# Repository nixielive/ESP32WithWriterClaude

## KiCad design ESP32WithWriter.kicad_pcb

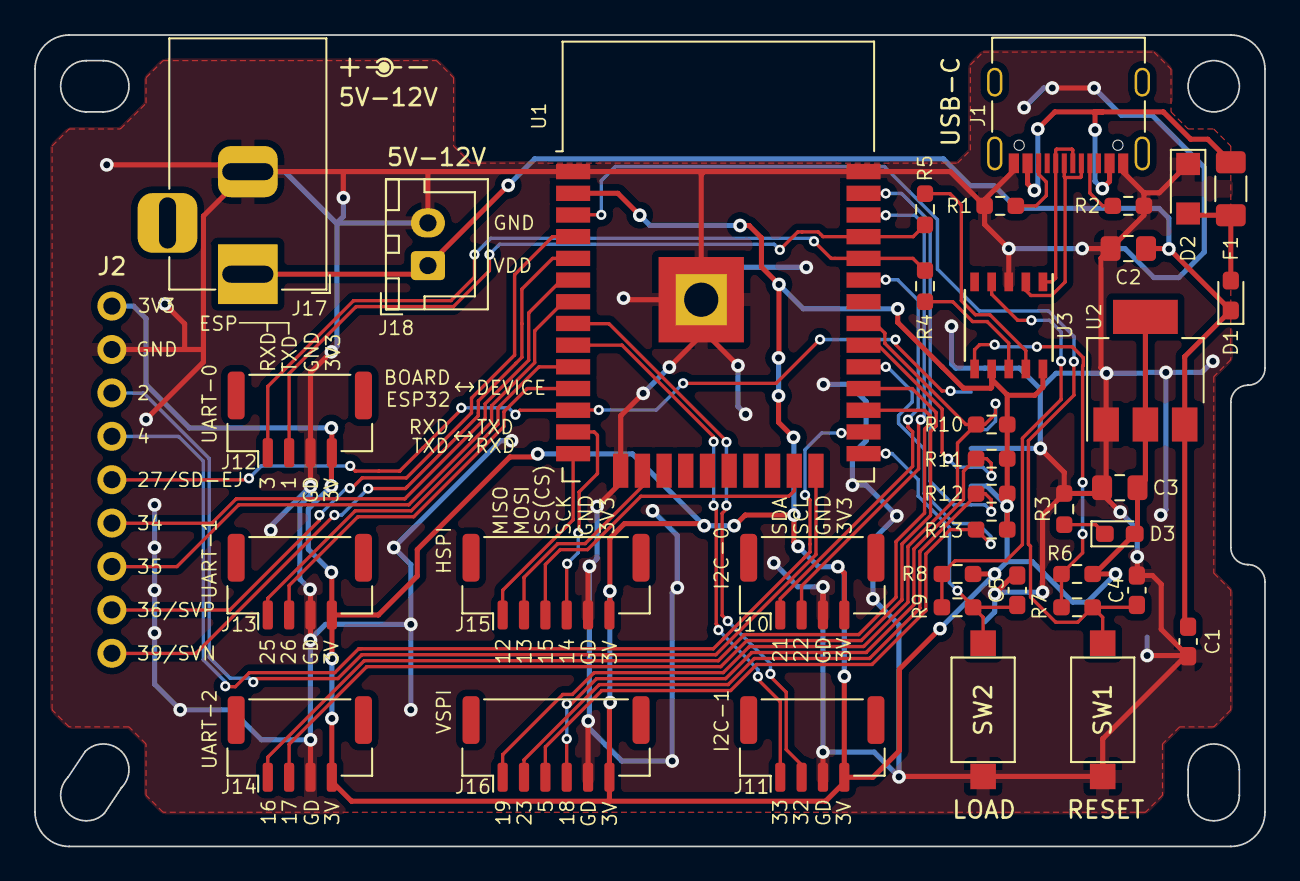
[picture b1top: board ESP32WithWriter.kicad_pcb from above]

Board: 2 copper layers, 72.0 x 47.5 mm, 39 parts (1 on the bottom side), 41 nets.

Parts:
C1: 105; C_0603_1608Metric_Pad1.08x0.95mm_HandSolder
C2, C3: 106; C_0805_2012Metric_Pad1.18x1.45mm_HandSolder
C4, C5: 103; C_0603_1608Metric_Pad1.08x0.95mm_HandSolder
D1: 1N5819; D_0603_1608Metric_Pad1.05x0.95mm_HandSolder
D2: SD05_SOD323; D_SMF
D3: RED; LED_0603_1608Metric_Pad1.05x0.95mm_HandSolder
F1: Polyfuse; R_1206_3216Metric_Pad1.30x1.75mm_HandSolder
J1: USB_C_Receptacle_USB2.0; USB_C_Receptacle_Palconn_UTC16-G
J2: Conn_01x09_Male; PinHeader_1x09_P2.54mm_Vertical
J7: Micro_SD_Card_Det; microSD_CTF-11081-P
J10, J11, J12, J13, J14: Conn_01x04_Male; JST_GH_BM04B-GHS-TBT_1x04-1MP_P1.25mm_Vertical
J15, J16: Conn_01x06_Male; JST_GH_BM06B-GHS-TBT_1x06-1MP_P1.25mm_Vertical
J17: Barrel_Jack_Switch; BarrelJack_Horizontal
J18: Conn_01x02_Male; JST_XH_B2B-XH-A_1x02_P2.50mm_Vertical
R1, R2: 5K1; R_0603_1608Metric_Pad0.98x0.95mm_HandSolder
R3: 392; R_0603_1608Metric_Pad0.98x0.95mm_HandSolder
R4, R5: 101; R_0603_1608Metric_Pad0.98x0.95mm_HandSolder
R6, R7, R8, R9, R10, R11, R12, R13: 103; R_0603_1608Metric_Pad0.98x0.95mm_HandSolder
SW1, SW2: SW_Push; SW_SPST_CK_RS282G05A3
U1: ESP32-WROOM-32D; ESP32-WROOM-32
U2: AMS1117-3.3; SOT-223-3_TabPin2
U3: CH340K; SSOP-10_3.9x4.9mm_P1.00mm

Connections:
DTR-H: R8.2, R9.1, U3.4 (~DTR)
ESP-RXD0: J12.1, R4.2, U1.34 (RXD0/IO3)
ESP-RXD1-V: J13.1, U1.10 (IO25)
ESP-RXD2: J14.1, U1.27 (IO16)
ESP-TXD0: J12.2, R5.2, U1.35 (TXD0/IO1)
ESP-TXD1-V: J13.2, U1.11 (IO26)
ESP-TXD2: J14.2, U1.28 (IO17)
ESP_EN: C4.1, R7.2, SW1.2, U1.3 (EN)
ESP_IO0: C5.1, R9.2, SW2.2, U1.25 (IO0)
GND: C1.2, C2.2, C3.2, C4.2, C5.2, D2.1 (A1), J1.A1 (GND), J1.A12 (GND), J1.B1 (GND), J1.B12 (GND), J2.2, J7.6 (VSS), J7.11 (SHIELD), J10.3, J11.3, J12.3, J13.3, J14.3, J15.5, J16.5, J17.2, J18.2, R1.2, R2.2, R3.2, SW1.1, SW2.1, U1.1 (GND), U1.15 (GND), U1.38 (GND), U1.39 (GND), U2.1 (GND), U3.3 (GND)
HSPI-MISO: J15.1, U1.14 (IO12)
HSPI-MOSI: J15.2, U1.16 (IO13)
HSPI-SCK: J15.4, U1.13 (IO14)
HSPI-SS(CS): J15.3, U1.23 (IO15)
I2C0-SCL: J10.2, U1.36 (IO22)
I2C0-SDA: J10.1, U1.33 (IO21)
I2C1-SCL: J11.2, U1.8 (IO32)
I2C1-SDA: J11.1, U1.9 (IO33)
IN34: J2.6, U1.6 (IO34)
IN35: J2.7, U1.7 (IO35)
IO2: J2.3, U1.24 (IO2)
IO4: J2.4, U1.26 (IO4)
IO27: J2.5, J7.9 (DET_B), U1.12 (IO27)
unnamed: D1.2 (A), D2.2 (A2), F1.2
unnamed: D3.1 (K), R3.1
unnamed: F1.1, J1.A4 (VBUS), J1.A9 (VBUS), J1.B4 (VBUS), J1.B9 (VBUS)
unnamed: R4.1, U3.8 (TXD)
unnamed: R5.1, U3.9 (RXD)
RTS-H: R6.2, R7.1, U3.6 (~RTS)
SD-CD: J7.2 (DAT3/CD), J16.3, R13.1, U1.29 (IO5)
SD-CLK: J7.5 (CLK), J16.4, R11.1, U1.30 (IO18)
SD-CMD: J7.3 (CMD), J16.2, R12.1, U1.37 (IO23)
SD-D0: J7.7 (DAT0), J16.1, R10.1, U1.31 (IO19)
SVN_IN39: J2.9, U1.5 (SENSOR_VN)
SVP_IN36: J2.8, U1.4 (SENSOR_VP)
USB-5V: C1.1, C2.1, D1.1 (K), J17.1, J18.1, U2.3 (VI)
USB-CC1: J1.B5 (CC2), R1.1
USB-CC2: J1.A5 (CC1), R2.1
USB-D+: J1.A6 (D+), J1.B6 (D+), U3.1 (UD+)
USB-D-: J1.A7 (D-), J1.B7 (D-), U3.2 (UD-)
VCC-3V3: C3.1, D3.2 (A), J2.1, J7.4 (VDD), J10.4, J11.4, J12.4, J13.4, J14.4, J15.6, J16.6, R6.1, R8.1, R10.2, R11.2, R12.2, R13.2, U1.2 (VDD), U2.2 (VO), U3.7 (VCC), U3.10 (V3)
